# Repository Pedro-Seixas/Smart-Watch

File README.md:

# Smart-Watch
A custom low-power stm32-based wearable smart watch

## Features
- 6-Axis IMU Sensor for motion detection and pedometer.
- Temperature Sensor
- OLED Display
- Powered by 3.7V battery or USB
- 2 programmable switches
- Real-Time Clock
- Tap Sensor

## Pinout Diagram

## Schematic

## PCB

## Demo (Clock | Menu | Sensors)

If you would like to clone the repo, see the "How to" in the Docs folder.

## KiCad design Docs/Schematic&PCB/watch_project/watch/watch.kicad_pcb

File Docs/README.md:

# How to get it working

## Softwares needed:
- STM32CubeIDE
- STM32CubeProgrammer

## Install necessary files
- Clone the repository to a folder and in STM32CubeIDE open the project

## Upload to the device
- Build the project and open STM32CubeProgrammer.
- Select USB since we are doing DFU (See 1).
- Click "Open File" and navigate to your project folder, go to the Debug folder and select the file with the .elf extension (See 2).
- Remove the device from the USB, hold the boot button (SW2) and connect the device to the computer. Release the boot button.
- Click the refresh icon in the STM32CubeProgrammer software (See 3), it should find the device. Now, click in "Connect" (See 4). Finally, click in "Download" (See 5).
- After the download is complete, press the Reset button (SW1) or remove and connect the USB.

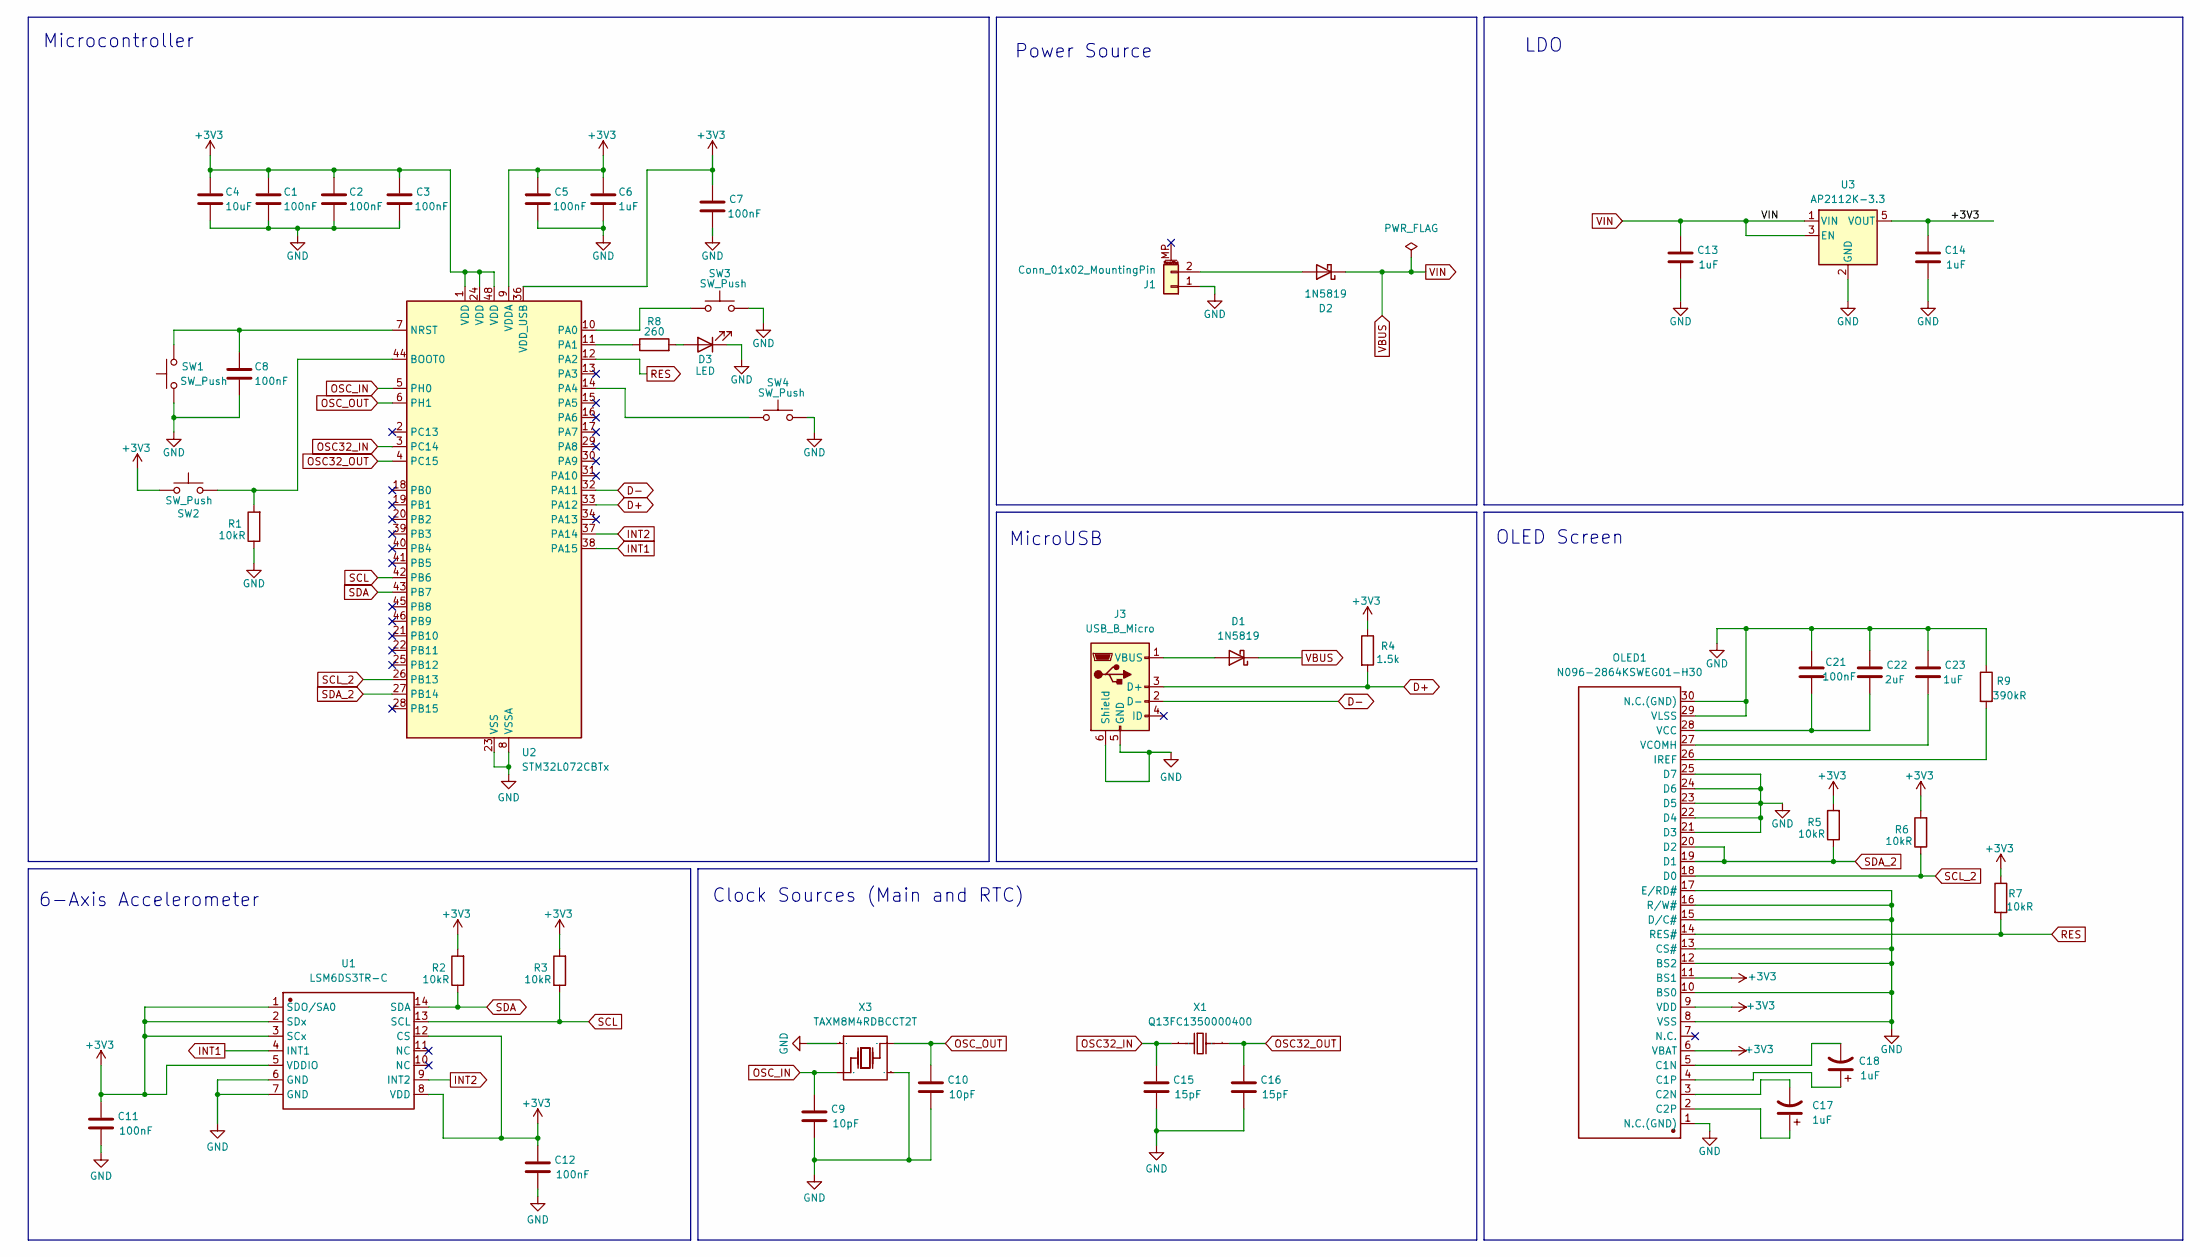
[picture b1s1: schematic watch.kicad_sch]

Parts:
C1, C2, C3, C5, C7, C8, C11, C12, C21: 100nF; C_0603_1608Metric
C4: 10uF; C_0603_1608Metric
C6, C13, C14, C17, C18, C23: 1uF; C_0805_2012Metric
C9, C10: 10pF; C_0402_1005Metric
C15, C16: 15pF; C_0402_1005Metric
C22: 2uF; C_0805_2012Metric
D1, D2: 1N5819; SOD-123_L2.7-W1.6-LS3.7-RD; JLC_3DModel 4d7f235d12124480ae44c354a7fd93dd
D3: LED; LED0805-R-RD
J1: Conn_01x02_MountingPin; HDR-TH_2P-P2.00-H-M_2005WR-2P; JLC_3DModel bbbe6f8a9a8948aa8046efa4a5376ae2
J3: USB_B_Micro; MICRO-USB-SMD_5P-P0.65-H-F_C10418; JLC_3DModel 8d98bdb22dfe41cea8df3303517703a8
OLED1: N096-2864KSWEG01-H30; OLED_0.96-30P-P0.70-12864; Manufacturer Part N096-2864KSWEG01-H30; JLC_3DModel 051045abecb44869adf3d7bdc1667540
R1, R2, R3, R5, R6, R7: 10kR; R_0805_2012Metric
R4: 1.5k; R_0603_1608Metric
R8: 260; R_0805_2012Metric
R9: 390kR; R_0805_2012Metric
SW1, SW2: SW_Push; SW-SMD_L3.9-W3.0-P4.45; JLC_3DModel 2e35dca8e7854ed683469f8d54d1ef17
SW3, SW4: SW_Push; SW-Horz
U1: LSM6DS3TR-C; LGA-14_L3.0-W2.5-P0.50-TL; Manufacturer Part LSM6DS3TR-C
U2: STM32L072CBTx; LQFP-48_7x7mm_P0.5mm
U3: AP2112K-3.3; SOT-23-5
X1: Q13FC1350000400; FC-135R_L3.2-W1.5; Manufacturer Part Q13FC13500004
X3: TAXM8M4RDBCCT2T; CRYSTAL-SMD_4P-L3.2-W2.5-BL; Manufacturer Part TAXM8M4RDBCCT2T

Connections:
+3V3: C1.1, C2.1, C3.1, C4.1, C5.1, C6.1, C7.1, C11.1, C12.1, C14.1, OLED1.6 (VBAT), OLED1.9 (VDD), OLED1.11 (BS1), R2.2, R3.2, R4.1, R5.2, R6.2, R7.1, SW2.1, U1.1 (SDO/SA0), U1.2 (SDx), U1.3 (SCx), U1.5 (VDDIO), U1.8 (VDD), U1.12 (CS), U2.1 (VDD), U2.9 (VDDA), U2.24 (VDD), U2.36 (VDD_USB), U2.48 (VDD), U3.5 (VOUT)
D+: J3.3 (D+), R4.2, U2.33 (PA12)
D-: J3.2 (D-), U2.32 (PA11)
GND: C1.2, C2.2, C3.2, C4.2, C5.2, C6.2, C7.2, C8.2, C9.2, C10.2, C11.2, C12.2, C13.2, C14.2, C15.2, C16.2, C21.1, C22.1, C23.1, D3.1 (K), J1.1, J3.5 (GND), J3.6 (Shield), OLED1.1 (N.C.(GND)), OLED1.8 (VSS), OLED1.10 (BS0), OLED1.12 (BS2), OLED1.13 (CS#), OLED1.15 (D/C#), OLED1.16 (R/W#), OLED1.17 (E/RD#), OLED1.21 (D3), OLED1.22 (D4), OLED1.23 (D5), OLED1.24 (D6), OLED1.25 (D7), OLED1.29 (VLSS), OLED1.30 (N.C.(GND)), R1.1, R9.1, SW1.1, SW3.2, SW4.2, U1.6 (GND), U1.7 (GND), U2.8 (VSSA), U2.23 (VSS), U2.35 (VSS), U2.47 (VSS), U3.2 (GND), X3.2, X3.4
INT1: U1.4 (INT1), U2.38 (PA15)
INT2: U1.9 (INT2), U2.37 (PA14)
unnamed: D1.2 (A), J3.1 (VBUS)
unnamed: D2.2 (A), J1.2
unnamed: D3.2 (A), R8.2
unnamed: C18.2, OLED1.5 (C1N)
unnamed: C18.1, OLED1.4 (C1P)
unnamed: C17.2, OLED1.3 (C2N)
unnamed: C17.1, OLED1.2 (C2P)
unnamed: OLED1.26 (IREF), R9.2
unnamed: C21.2, C22.2, OLED1.28 (VCC)
unnamed: C23.2, OLED1.27 (VCOMH)
unnamed: R1.2, SW2.2, U2.44 (BOOT0)
unnamed: C8.1, SW1.2, U2.7 (NRST)
unnamed: SW3.1, U2.10 (PA0)
unnamed: R8.1, U2.11 (PA1)
unnamed: SW4.1, U2.14 (PA4)
OSC32_IN: C15.1, U2.3 (PC14), X1.1
OSC32_OUT: C16.1, U2.4 (PC15), X1.2
OSC_IN: C9.1, U2.5 (PH0), X3.1
OSC_OUT: C10.1, U2.6 (PH1), X3.3
RES: OLED1.14 (RES#), R7.2, U2.12 (PA2)
SCL: R3.1, U1.13 (SCL), U2.42 (PB6)
SCL_2: OLED1.18 (D0), R6.1, U2.26 (PB13)
SDA: R2.1, U1.14 (SDA), U2.43 (PB7)
SDA_2: OLED1.19 (D1), OLED1.20 (D2), R5.1, U2.27 (PB14)
VBUS: C13.1, D1.1 (K), D2.1 (K), U3.1 (VIN), U3.3 (EN)

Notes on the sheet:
LDO
MicroUSB
Power Source
Clock Sources (Main and RTC)
6-Axis Accelerometer
OLED Screen
Microcontroller

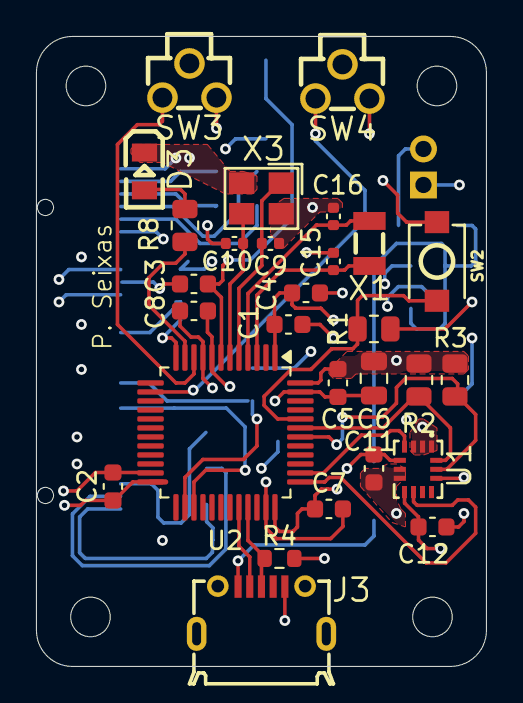
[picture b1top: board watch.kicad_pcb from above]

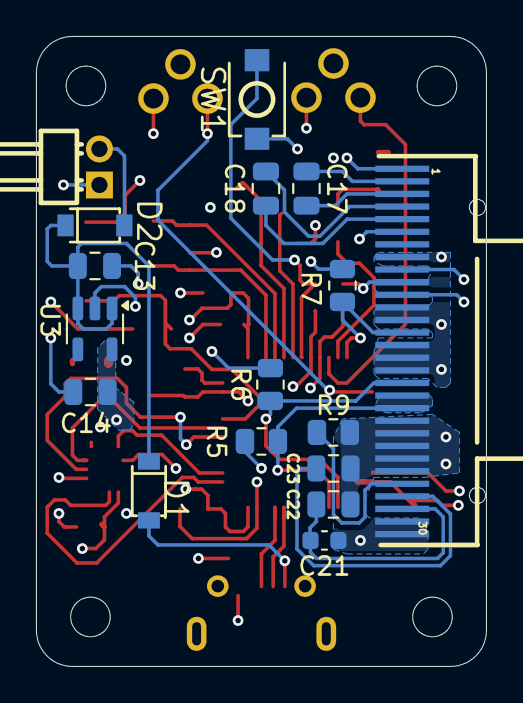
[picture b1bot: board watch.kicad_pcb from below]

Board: 4 copper layers, 25.0 x 35.0 mm, 45 parts (17 on the bottom side), 31 nets.

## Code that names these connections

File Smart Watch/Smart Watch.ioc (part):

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Mcu.Name=STM32L072C(B-Z)Tx
Mcu.Package=LQFP48
Mcu.UserName=STM32L072CBTx
PA0.GPIOParameters=GPIO_PuPd,GPIO_ModeDefaultEXTI
PA0.GPIO_ModeDefaultEXTI=GPIO_MODE_IT_RISING
PA0.GPIO_PuPd=GPIO_PULLUP
PA0.Signal=GPXTI0
PA1.GPIOParameters=GPIO_Speed,GPIO_PuPd
PA1.GPIO_PuPd=GPIO_NOPULL
PA1.GPIO_Speed=GPIO_SPEED_FREQ_LOW
PA1.Signal=GPIO_Output
PA11.Mode=Device
PA11.Signal=USB_DM
PA12.Mode=Device
PA12.Signal=USB_DP
PA15.Signal=GPXTI15
PA2.Signal=GPIO_Output
PA4.GPIOParameters=GPIO_PuPd
PA4.GPIO_PuPd=GPIO_PULLUP
PA4.Signal=GPIO_Input
PB13.Mode=I2C
PB13.Signal=I2C2_SCL
PB14.Mode=I2C
PB14.Signal=I2C2_SDA
PB6.Mode=I2C
PB6.Signal=I2C1_SCL
PB7.Mode=I2C
PB7.Signal=I2C1_SDA
PC14-OSC32_IN.Mode=LSE-External-Oscillator
PC14-OSC32_IN.Signal=RCC_OSC32_IN
PC15-OSC32_OUT.Mode=LSE-External-Oscillator
PC15-OSC32_OUT.Signal=RCC_OSC32_OUT
PH0-OSC_IN.Mode=HSE-External-Oscillator
PH0-OSC_IN.Signal=RCC_OSC_IN
PH1-OSC_OUT.Mode=HSE-External-Oscillator
PH1-OSC_OUT.Signal=RCC_OSC_OUT
RCC.HSE_VALUE=8000000
RCC.SYSCLKFreq_VALUE=32000000
RCC.SYSCLKSource=RCC_SYSCLKSOURCE_PLLCLK
board=custom

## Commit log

2025-07-14 add .gitignore
2025-07-14 Add project files
2025-07-14 Fix gitignore
2025-07-14 Fix gitignore once more
2025-07-21 Added Test Code for RTC - Works
2025-07-21 Added PINOUT
2025-07-21 Added LSE to RTC & Clock Display Logic
2025-07-21 Added FreeRTOS and main tasks
2025-07-21 Added more Stack to Main Task
2025-07-21 Added PCB to README
2025-07-23 Added a Sketch of Menu & EXTIs
2025-07-24 Added Menu Selection Logic
2025-07-25 Fixed Black Screen Bug in Menu
2025-07-25 Added Portrait Mode to ssd1306 library
2025-07-26 Added Sensors Page but Needs Work
2025-07-26 Fixed Sensors Page, Working on Temp
2025-07-26 Temporarily Removed Temp - Not reliable
2025-07-27 Commented out the update function by mistake
2025-07-27 Added Change Time Page
2025-07-27 Added Page Exit Logic but Needs Refining
2025-07-28 Added Ability to Edit Time
2025-07-28 TODO: Swap buttons
2025-07-28 Buttons Swapped
2025-07-28 Double Increment Bug Found - Even after Deboucing
2025-07-28 Solved Small Bug in Sensors Page
2025-07-29 Solved a small bug in sensors page
2025-07-29 Solved double-increment bug
2025-07-29 Added Demo Photos to README
2025-07-29 Removed Unnecessary While Loop
2025-07-30 Added Datasheets to Repo
2025-07-30 Added pedometer logic, needs integrating
2025-07-31 Added pedometer to the sensors page
2025-08-01 Testing turning on/off display
2025-08-01 Testing Wrist Tilt Functionality - No Success
2025-08-01 Wrist tilt detection working, needs adjust
2025-08-01 Tilting Detection works, needs integrating
2025-08-01 TODO: add registers name in a separate file
2025-08-01 Started naming registers following standard
2025-08-01 Added functions and registers to header file
2025-08-01 Identation problem?
2025-08-01 Github geeking with tabs
2025-08-04 Separating Logic Into Files
2025-08-04 Added function to write to ctrl10 so we dont override the reg
2025-08-04 Wrist tilt to turn on the screen added
2025-08-04 Display on/off if inactive logic added
2025-08-04 Simplified button logic & solved a bug
2025-08-04 Start adding tap detection, currently not working
2025-08-04 Could not find problem with tap detection
2025-08-04 Why no work
2025-08-05 Tap Detection Working - Needs adjuments
2025-08-05 Increased tap intensity ths
2025-08-05 formatting
2025-08-07 Added Schematics, PCB and BOM
2025-08-07 Added LDO datasheet
2025-08-07 Replaced write register functions
2025-08-07 Added I2C port as a global variable
2025-08-07 Added unions to remove visual code atrocities
2025-08-07 Identation fix
2025-08-07 Fixed bug in sensors page
2025-08-07 Added double-tap to turn on/off display
2025-08-08 Added "how to get it working"
2025-08-08 Fixed a bug and better naming
2025-08-08 Updated pinout
2025-08-08 Added register read func & found a bug
2025-08-09 Double taps works only in one axis now
2025-08-12 Typo
